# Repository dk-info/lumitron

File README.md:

# lumitron
introduction to electronics

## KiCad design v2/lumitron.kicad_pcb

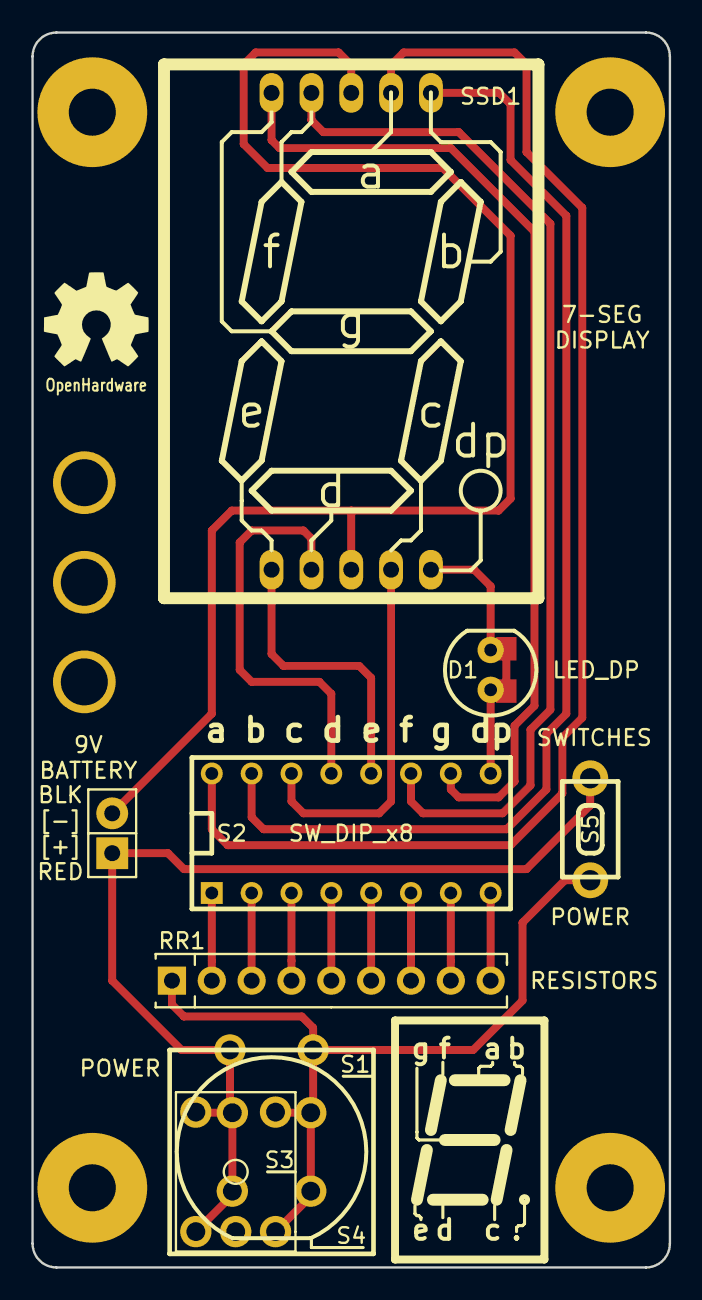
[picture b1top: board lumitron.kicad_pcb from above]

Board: 2 copper layers, 40.6 x 78.7 mm, 18 parts (1 on the bottom side), 19 nets.

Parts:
BT1: 9V_CONN; Pin_Header_Straight_1x02
BT2: 9V_PP3
D1: LED_DP; LED-5MM_SMD
G1: OSHW; OSHW_6mm
H1, H2, H3, H4: MTG_H; MountingHole_3-7mm
H5, H6, H7: Hole; MountingHole_3-4mm
RR1: RR8_330; SIP9_Housing
S1: POWER; sw_gpst
S2: SW_DIP_x8; DIP-16__300
S3: POWER3; sw_KSA_Tactile_SPST
S4: POWER2; sw_KS-01Q
S5: POWER; switch_MJTP1250
SSD1: SC10-21SRWA; 7SegmentLED

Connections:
/RES: RR1.1, S1.2, S3.2, S4.2, S4.4, S5.2
/[+]: BT1.1, S1.1, S3.1, S4.1, S4.3, S5.1
/[-]: BT1.2, SSD1.3, SSD1.8
/a: S2.16, SSD1.7
/b: S2.15, SSD1.6
/c: S2.14, SSD1.4
/d: S2.13, SSD1.2
/dp: D1.1, D1.2, S2.9, SSD1.5
/e: S2.12, SSD1.1
/f: S2.11, SSD1.9
/g: S2.10, SSD1.10
unnamed: RR1.2, S2.1
unnamed: RR1.3, S2.2
unnamed: RR1.4, S2.3
unnamed: RR1.5, S2.4
unnamed: RR1.6, S2.5
unnamed: RR1.7, S2.6
unnamed: RR1.8, S2.7
unnamed: RR1.9, S2.8

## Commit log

2017-09-16 lumitron first commit
2017-09-16 v2 HW of lumitron, slim version
2017-09-16 v2 HW updated images
2017-09-17 track layout cleanup
2017-09-17 added open source logo
2017-09-18 last cleanup before prototype
2017-09-19 reverse LED DP D1 silk legend fixed
2017-09-19 added BoM, silk legend cleanup
2017-09-19 added seeed PCB specifications
2017-09-20 update bom for standoffs
2017-09-20 move dipswitch to dnp
2017-09-20 updated BoM
2017-09-25 slots to holes, fix legend errors
2017-09-25 added Power momentary push button
2017-10-03 added momentary pushbutton for POWER
2017-10-09 BoM modified
2017-10-12 Test Plan
